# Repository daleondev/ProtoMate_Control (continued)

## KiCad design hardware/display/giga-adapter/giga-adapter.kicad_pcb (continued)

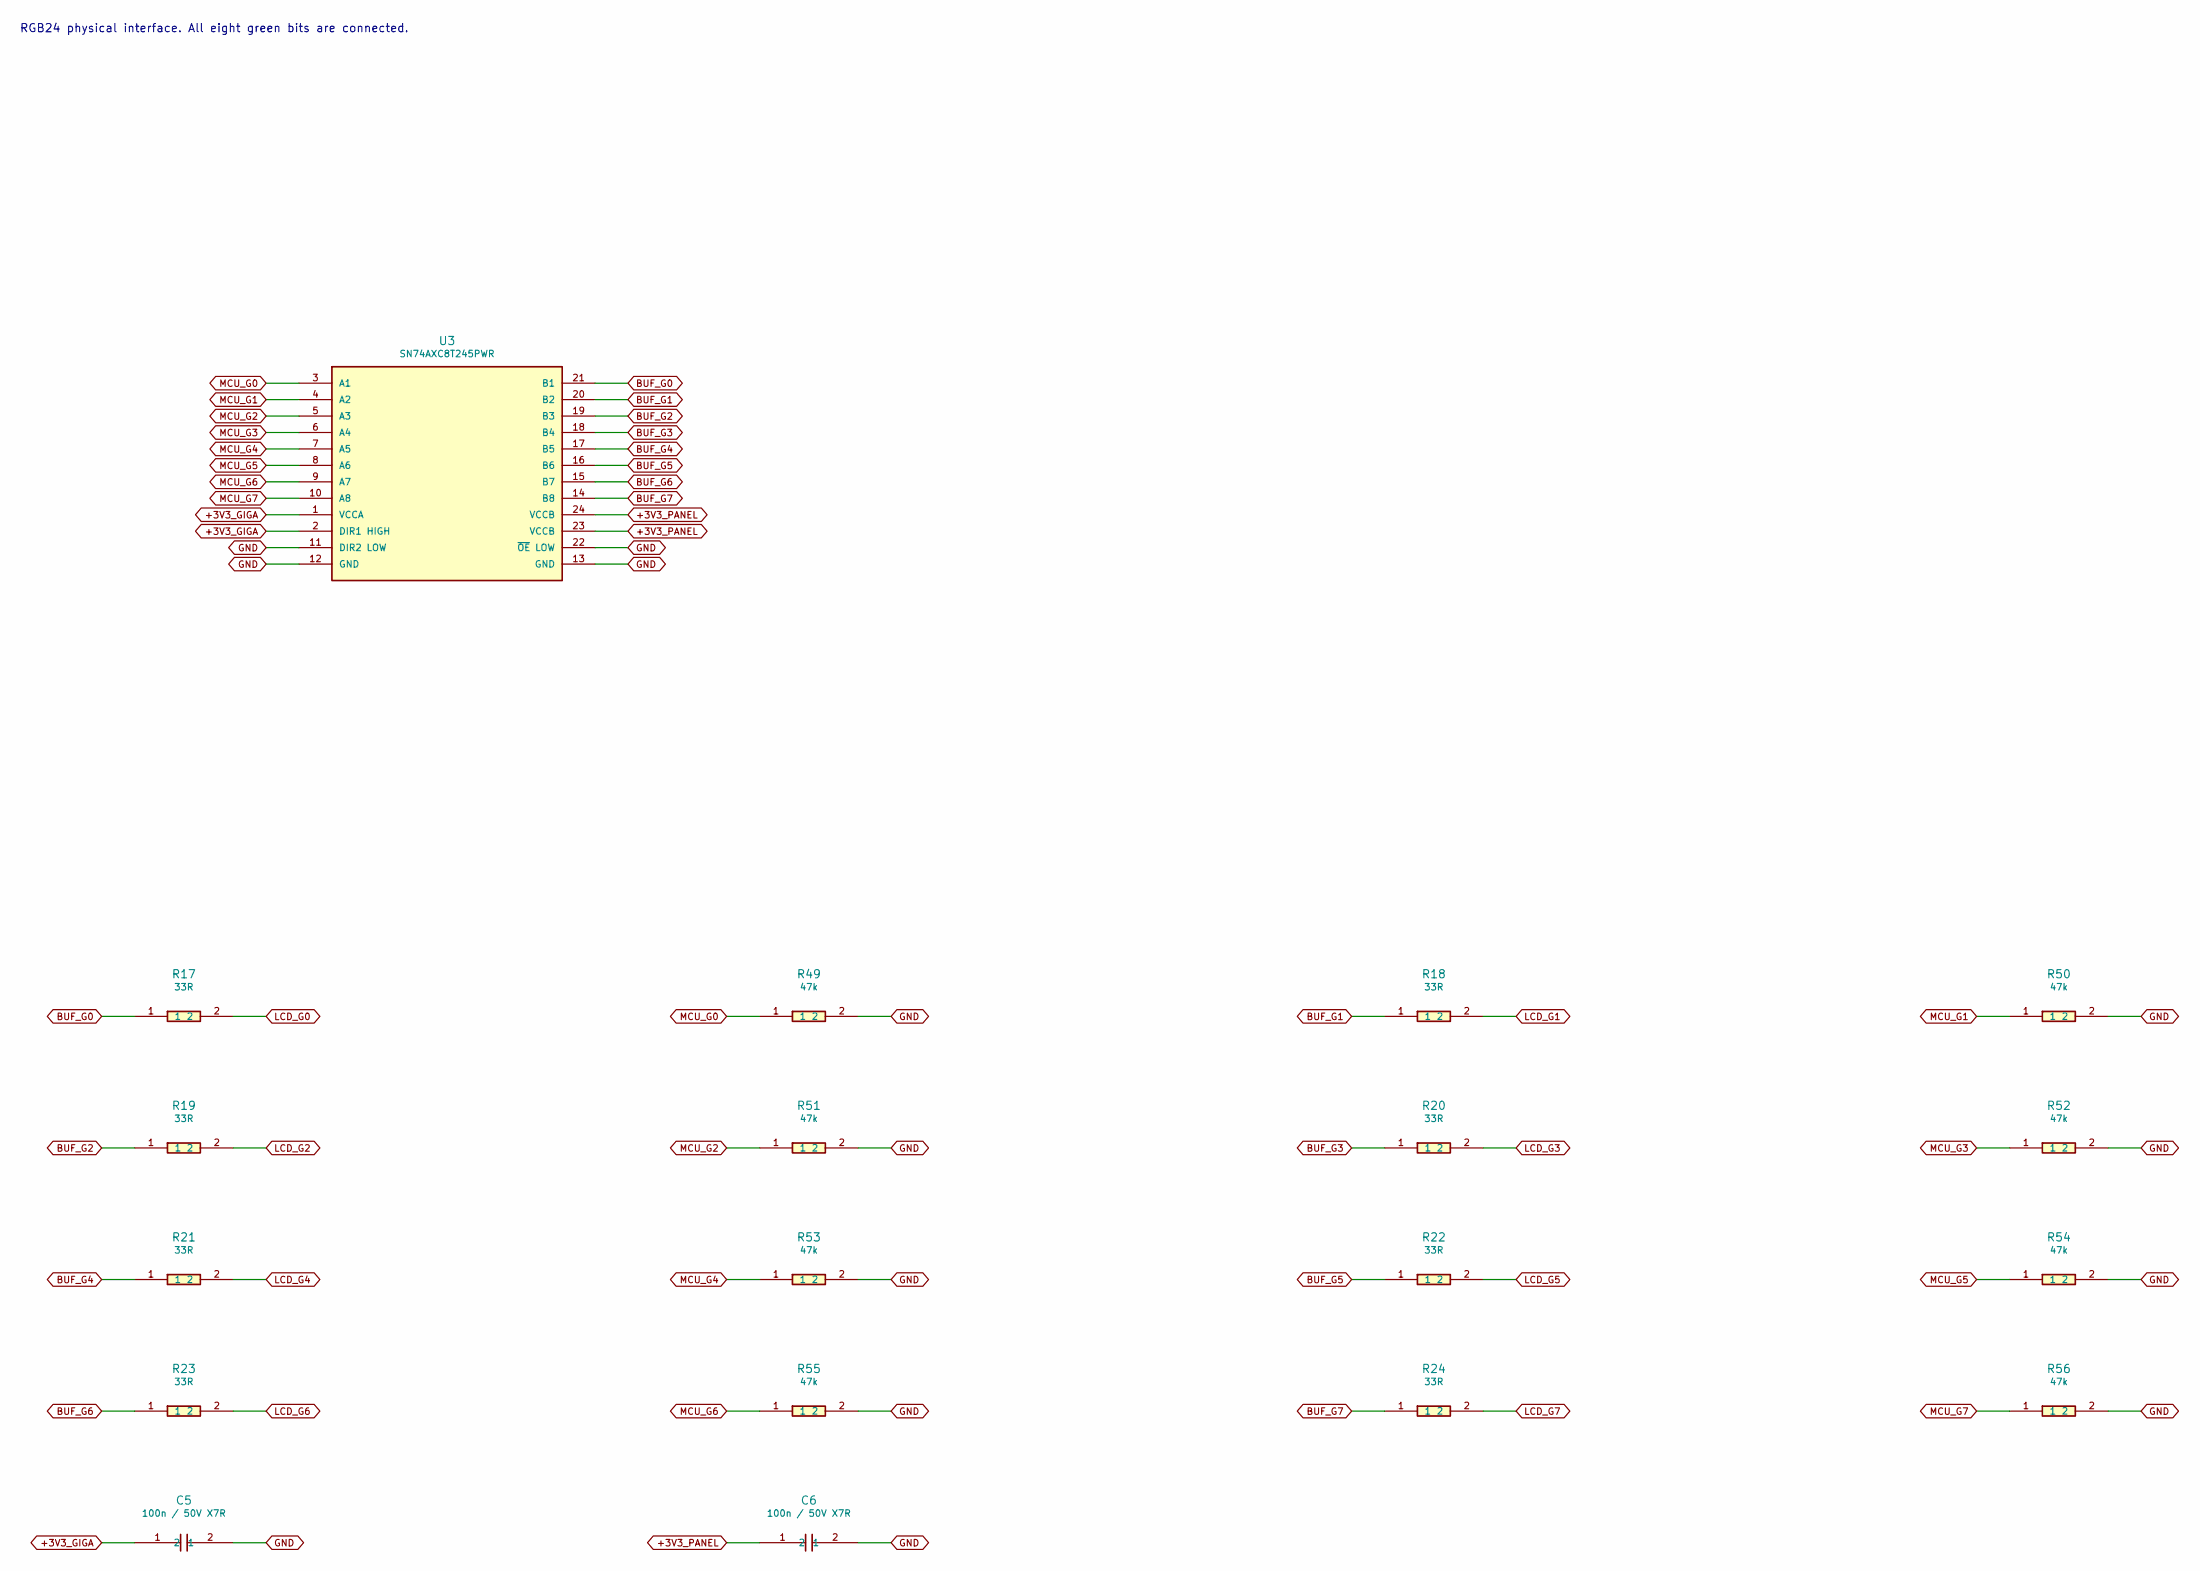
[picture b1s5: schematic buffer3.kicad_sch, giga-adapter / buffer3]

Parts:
C5, C6: 100n / 50V X7R; C_0603_1608Metric; MPN C0603C104K5RACTU
R17, R18, R19, R20, R21, R22, R23, R24: 33R; R_0402_1005Metric; MPN RC0402FR-0733RL
R49, R50, R51, R52, R53, R54, R55, R56: 47k; R_0402_1005Metric; MPN RC0402FR-0747KL
U3: SN74AXC8T245PWR; TSSOP-24_4.4x7.8mm_P0.65mm; MPN SN74AXC8T245PWR

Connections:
+3V3_GIGA: C5.1, U3.1 (VCCA), U3.2 (DIR1 HIGH); also elsewhere on the board
+3V3_PANEL: C6.1, U3.23 (VCCB), U3.24 (VCCB); also elsewhere on the board
BUF_G0: R17.1, U3.21 (B1)
BUF_G1: R18.1, U3.20 (B2)
BUF_G2: R19.1, U3.19 (B3)
BUF_G3: R20.1, U3.18 (B4)
BUF_G4: R21.1, U3.17 (B5)
BUF_G5: R22.1, U3.16 (B6)
BUF_G6: R23.1, U3.15 (B7)
BUF_G7: R24.1, U3.14 (B8)
GND: C5.2, C6.2, R49.2, R50.2, R51.2, R52.2, R53.2, R54.2, R55.2, R56.2, U3.11 (DIR2 LOW), U3.12 (GND), U3.13 (GND), U3.22 (~OE LOW); also elsewhere on the board
LCD_G0: R17.2; also elsewhere on the board
LCD_G1: R18.2; also elsewhere on the board
LCD_G2: R19.2; also elsewhere on the board
LCD_G3: R20.2; also elsewhere on the board
LCD_G4: R21.2; also elsewhere on the board
LCD_G5: R22.2; also elsewhere on the board
LCD_G6: R23.2; also elsewhere on the board
LCD_G7: R24.2; also elsewhere on the board
MCU_G0: R49.1, U3.3 (A1); also elsewhere on the board
MCU_G1: R50.1, U3.4 (A2); also elsewhere on the board
MCU_G2: R51.1, U3.5 (A3); also elsewhere on the board
MCU_G3: R52.1, U3.6 (A4); also elsewhere on the board
MCU_G4: R53.1, U3.7 (A5); also elsewhere on the board
MCU_G5: R54.1, U3.8 (A6); also elsewhere on the board
MCU_G6: R55.1, U3.9 (A7); also elsewhere on the board
MCU_G7: R56.1, U3.10 (A8); also elsewhere on the board

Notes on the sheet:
RGB24 physical interface. All eight green bits are connected.

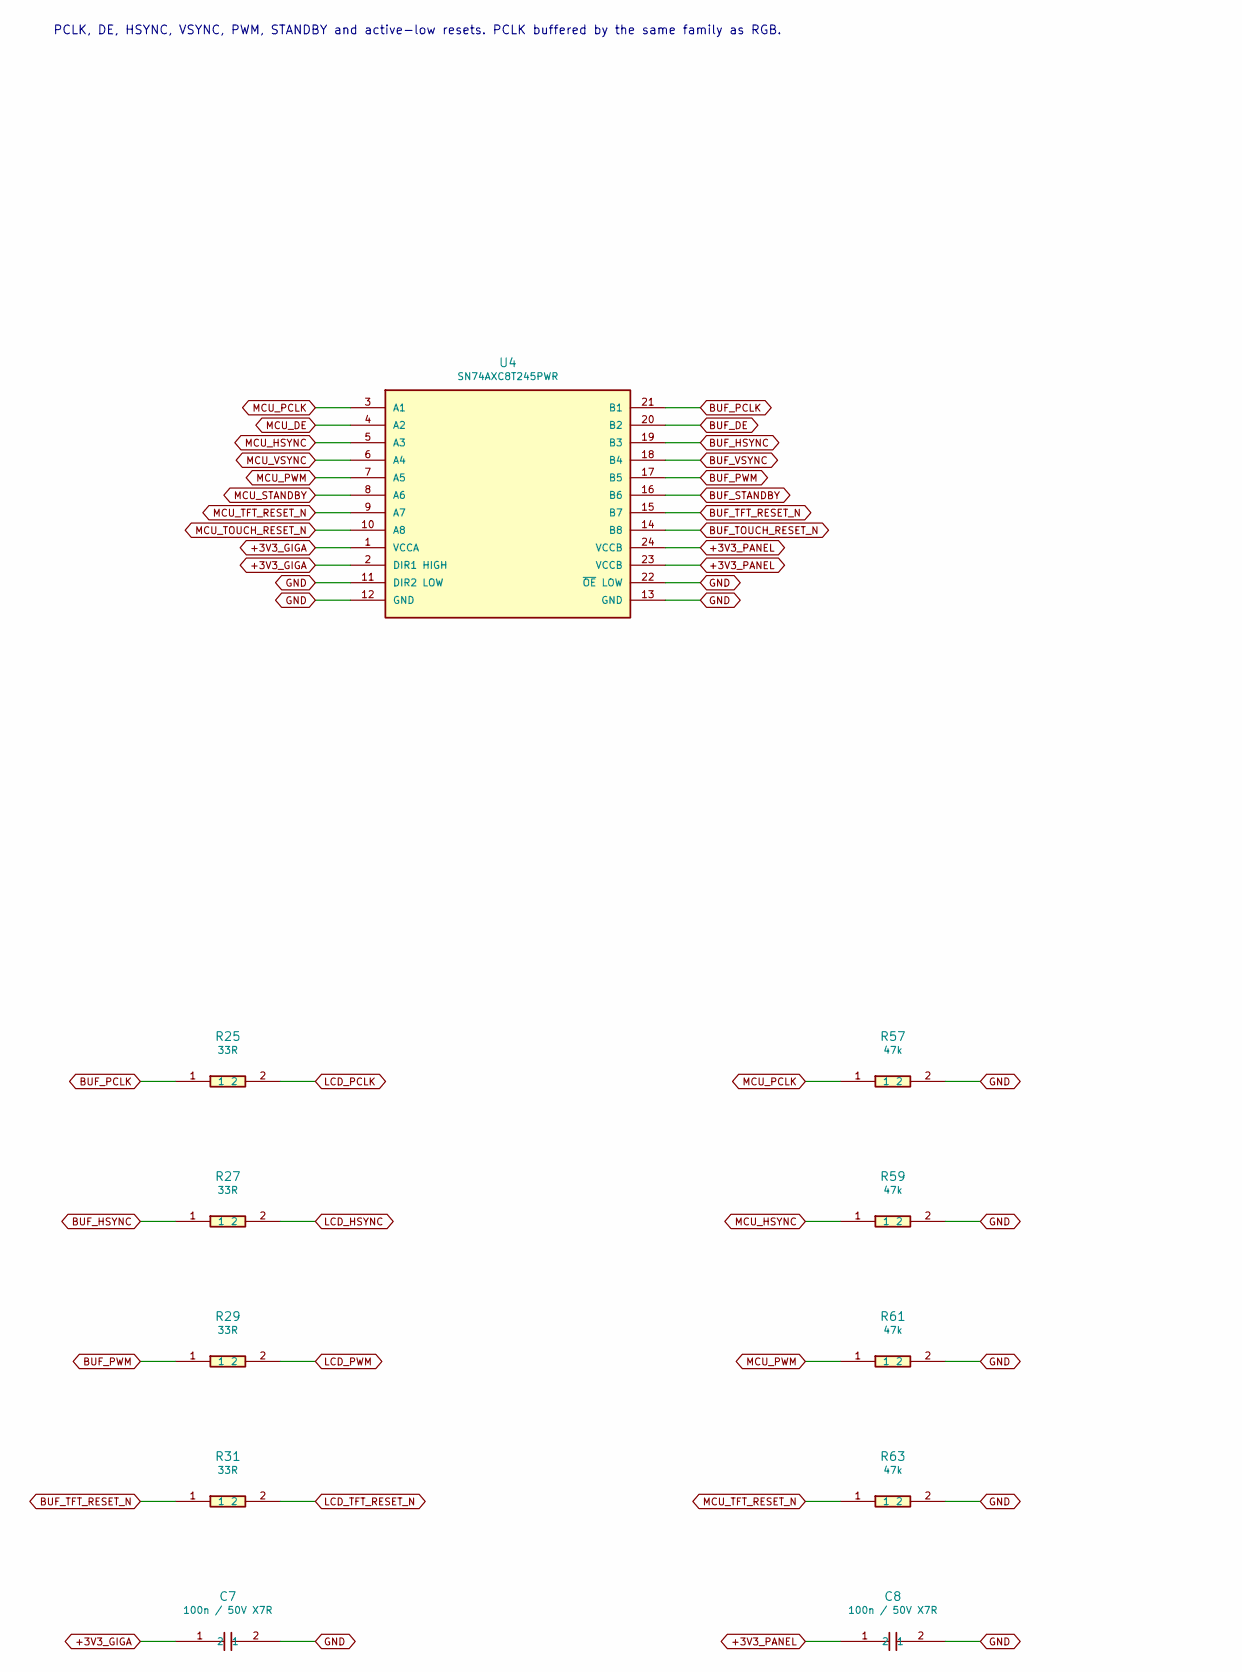
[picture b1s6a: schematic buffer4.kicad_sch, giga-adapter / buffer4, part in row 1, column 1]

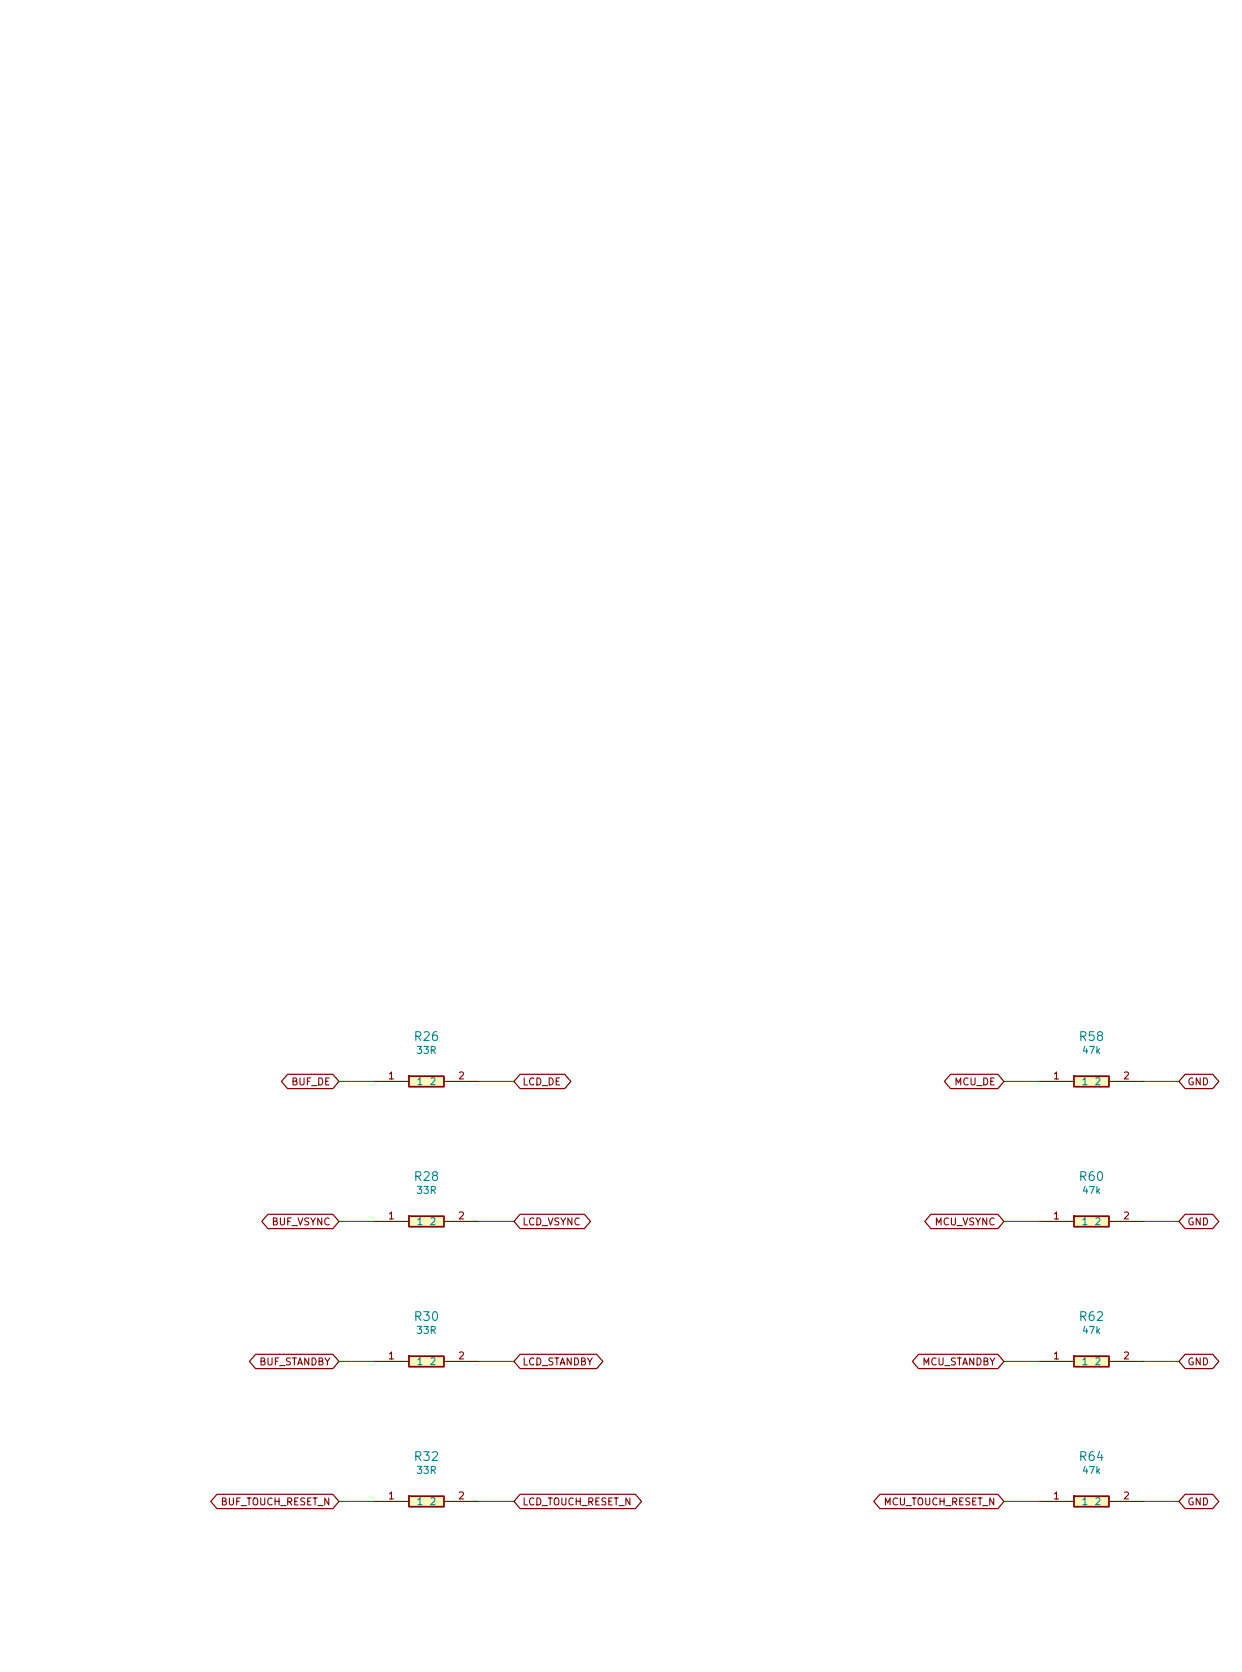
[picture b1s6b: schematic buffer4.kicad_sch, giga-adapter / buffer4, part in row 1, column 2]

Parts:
C7, C8: 100n / 50V X7R; C_0603_1608Metric; MPN C0603C104K5RACTU
R25, R26, R27, R28, R29, R30, R31, R32: 33R; R_0402_1005Metric; MPN RC0402FR-0733RL
R57, R58, R59, R60, R61, R62, R63, R64: 47k; R_0402_1005Metric; MPN RC0402FR-0747KL
U4: SN74AXC8T245PWR; TSSOP-24_4.4x7.8mm_P0.65mm; MPN SN74AXC8T245PWR

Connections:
+3V3_GIGA: C7.1, U4.1 (VCCA), U4.2 (DIR1 HIGH); also elsewhere on the board
+3V3_PANEL: C8.1, U4.23 (VCCB), U4.24 (VCCB); also elsewhere on the board
BUF_DE: R26.1, U4.20 (B2)
BUF_HSYNC: R27.1, U4.19 (B3)
BUF_PCLK: R25.1, U4.21 (B1)
BUF_PWM: R29.1, U4.17 (B5)
BUF_STANDBY: R30.1, U4.16 (B6)
BUF_TFT_RESET_N: R31.1, U4.15 (B7)
BUF_TOUCH_RESET_N: R32.1, U4.14 (B8)
BUF_VSYNC: R28.1, U4.18 (B4)
GND: C7.2, C8.2, R57.2, R58.2, R59.2, R60.2, R61.2, R62.2, R63.2, R64.2, U4.11 (DIR2 LOW), U4.12 (GND), U4.13 (GND), U4.22 (~OE LOW); also elsewhere on the board
LCD_DE: R26.2; also elsewhere on the board
LCD_HSYNC: R27.2; also elsewhere on the board
LCD_PCLK: R25.2; also elsewhere on the board
LCD_PWM: R29.2; also elsewhere on the board
LCD_STANDBY: R30.2; also elsewhere on the board
LCD_TFT_RESET_N: R31.2; also elsewhere on the board
LCD_TOUCH_RESET_N: R32.2; also elsewhere on the board
LCD_VSYNC: R28.2; also elsewhere on the board
MCU_DE: R58.1, U4.4 (A2); also elsewhere on the board
MCU_HSYNC: R59.1, U4.5 (A3); also elsewhere on the board
MCU_PCLK: R57.1, U4.3 (A1); also elsewhere on the board
MCU_PWM: R61.1, U4.7 (A5); also elsewhere on the board
MCU_STANDBY: R62.1, U4.8 (A6); also elsewhere on the board
MCU_TFT_RESET_N: R63.1, U4.9 (A7); also elsewhere on the board
MCU_TOUCH_RESET_N: R64.1, U4.10 (A8); also elsewhere on the board
MCU_VSYNC: R60.1, U4.6 (A4); also elsewhere on the board

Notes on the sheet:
PCLK, DE, HSYNC, VSYNC, PWM, STANDBY and active-low resets. PCLK buffered by the same family as RGB.

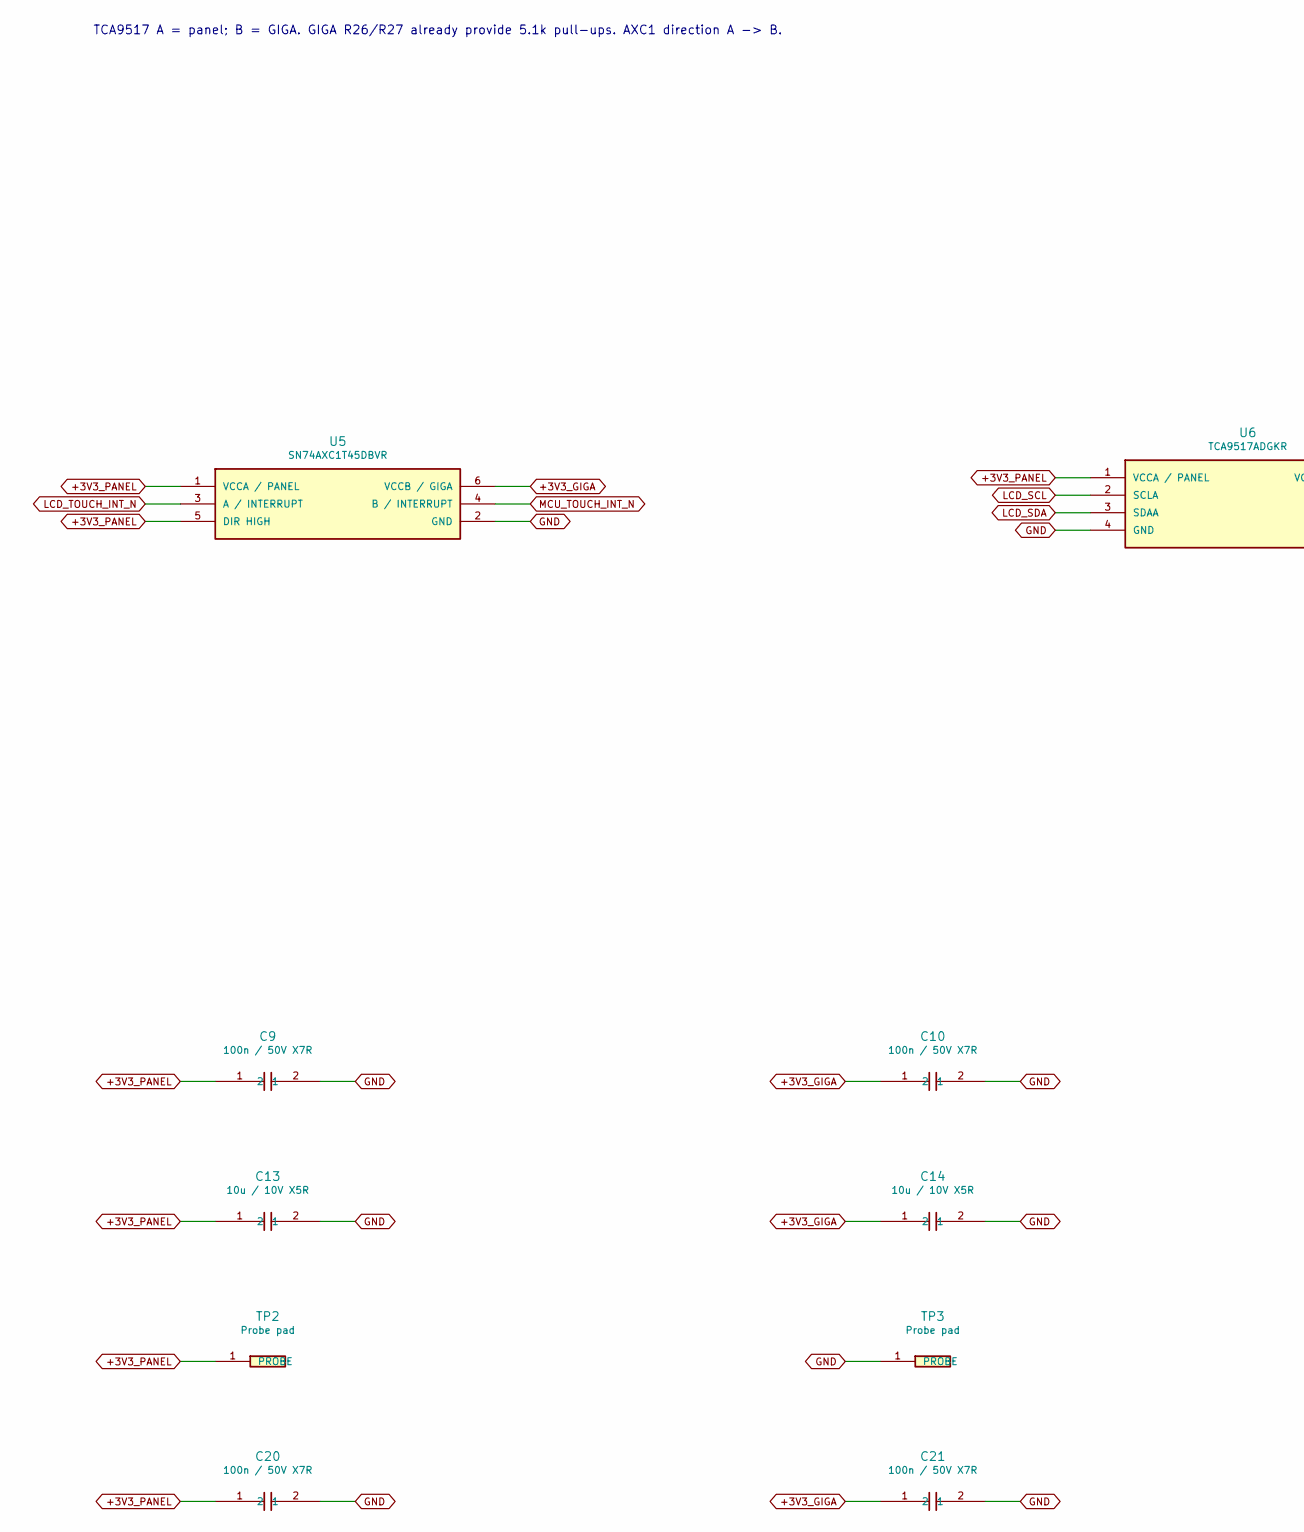
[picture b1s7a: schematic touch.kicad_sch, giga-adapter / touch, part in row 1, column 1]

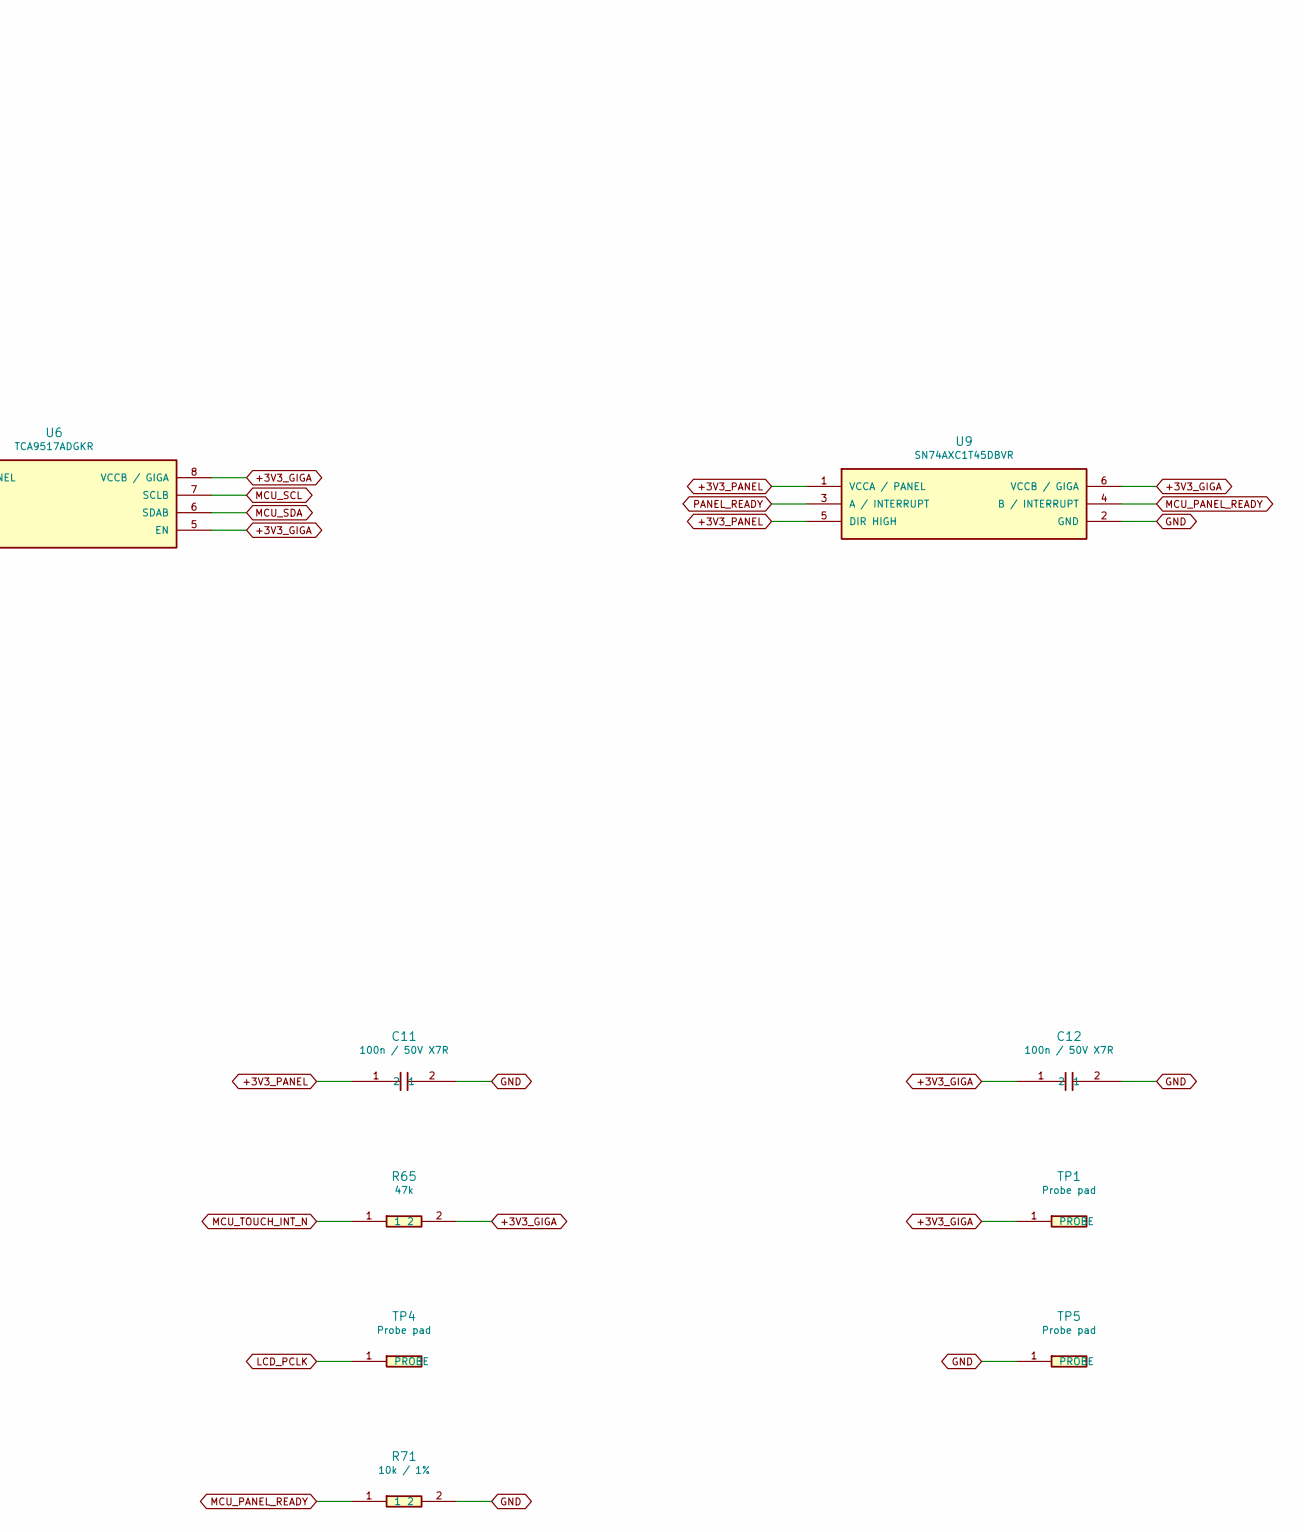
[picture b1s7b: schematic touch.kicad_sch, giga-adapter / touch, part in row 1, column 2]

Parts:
C9, C10, C11, C12, C20, C21: 100n / 50V X7R; C_0603_1608Metric; MPN C0603C104K5RACTU
C13, C14: 10u / 10V X5R; C_0805_2012Metric; MPN C0805C106K8PACTU
R65: 47k; R_0402_1005Metric; MPN RC0402FR-0747KL
R71: 10k / 1%; R_0603_1608Metric; MPN RC0603FR-0710KL
TP1, TP2, TP3, TP4, TP5: Probe pad; TestPoint_1.0mm; MPN PCB copper feature
U5, U9: SN74AXC1T45DBVR; SOT-23-6; MPN SN74AXC1T45DBVR
U6: TCA9517ADGKR; VSSOP-8_3x3mm_P0.65mm; MPN TCA9517ADGKR

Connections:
+3V3_GIGA: C10.1, C12.1, C14.1, C21.1, R65.2, TP1.1, U5.6 (VCCB / GIGA), U6.5 (EN), U6.8 (VCCB / GIGA), U9.6 (VCCB / GIGA); also elsewhere on the board
+3V3_PANEL: C9.1, C11.1, C13.1, C20.1, TP2.1, U5.1 (VCCA / PANEL), U5.5 (DIR HIGH), U6.1 (VCCA / PANEL), U9.1 (VCCA / PANEL), U9.5 (DIR HIGH); also elsewhere on the board
GND: C9.2, C10.2, C11.2, C12.2, C13.2, C14.2, C20.2, C21.2, R71.2, TP3.1, TP5.1, U5.2 (GND), U6.4 (GND), U9.2 (GND); also elsewhere on the board
LCD_PCLK: TP4.1; also elsewhere on the board
LCD_SCL: U6.2 (SCLA); also elsewhere on the board
LCD_SDA: U6.3 (SDAA); also elsewhere on the board
LCD_TOUCH_INT_N: U5.3 (A / INTERRUPT); also elsewhere on the board
MCU_PANEL_READY: R71.1, U9.4 (B / INTERRUPT); also elsewhere on the board
MCU_SCL: U6.7 (SCLB); also elsewhere on the board
MCU_SDA: U6.6 (SDAB); also elsewhere on the board
MCU_TOUCH_INT_N: R65.1, U5.4 (B / INTERRUPT); also elsewhere on the board
PANEL_READY: U9.3 (A / INTERRUPT); also elsewhere on the board

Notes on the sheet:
TCA9517 A = panel; B = GIGA. GIGA R26/R27 already provide 5.1k pull-ups. AXC1 direction A -> B.

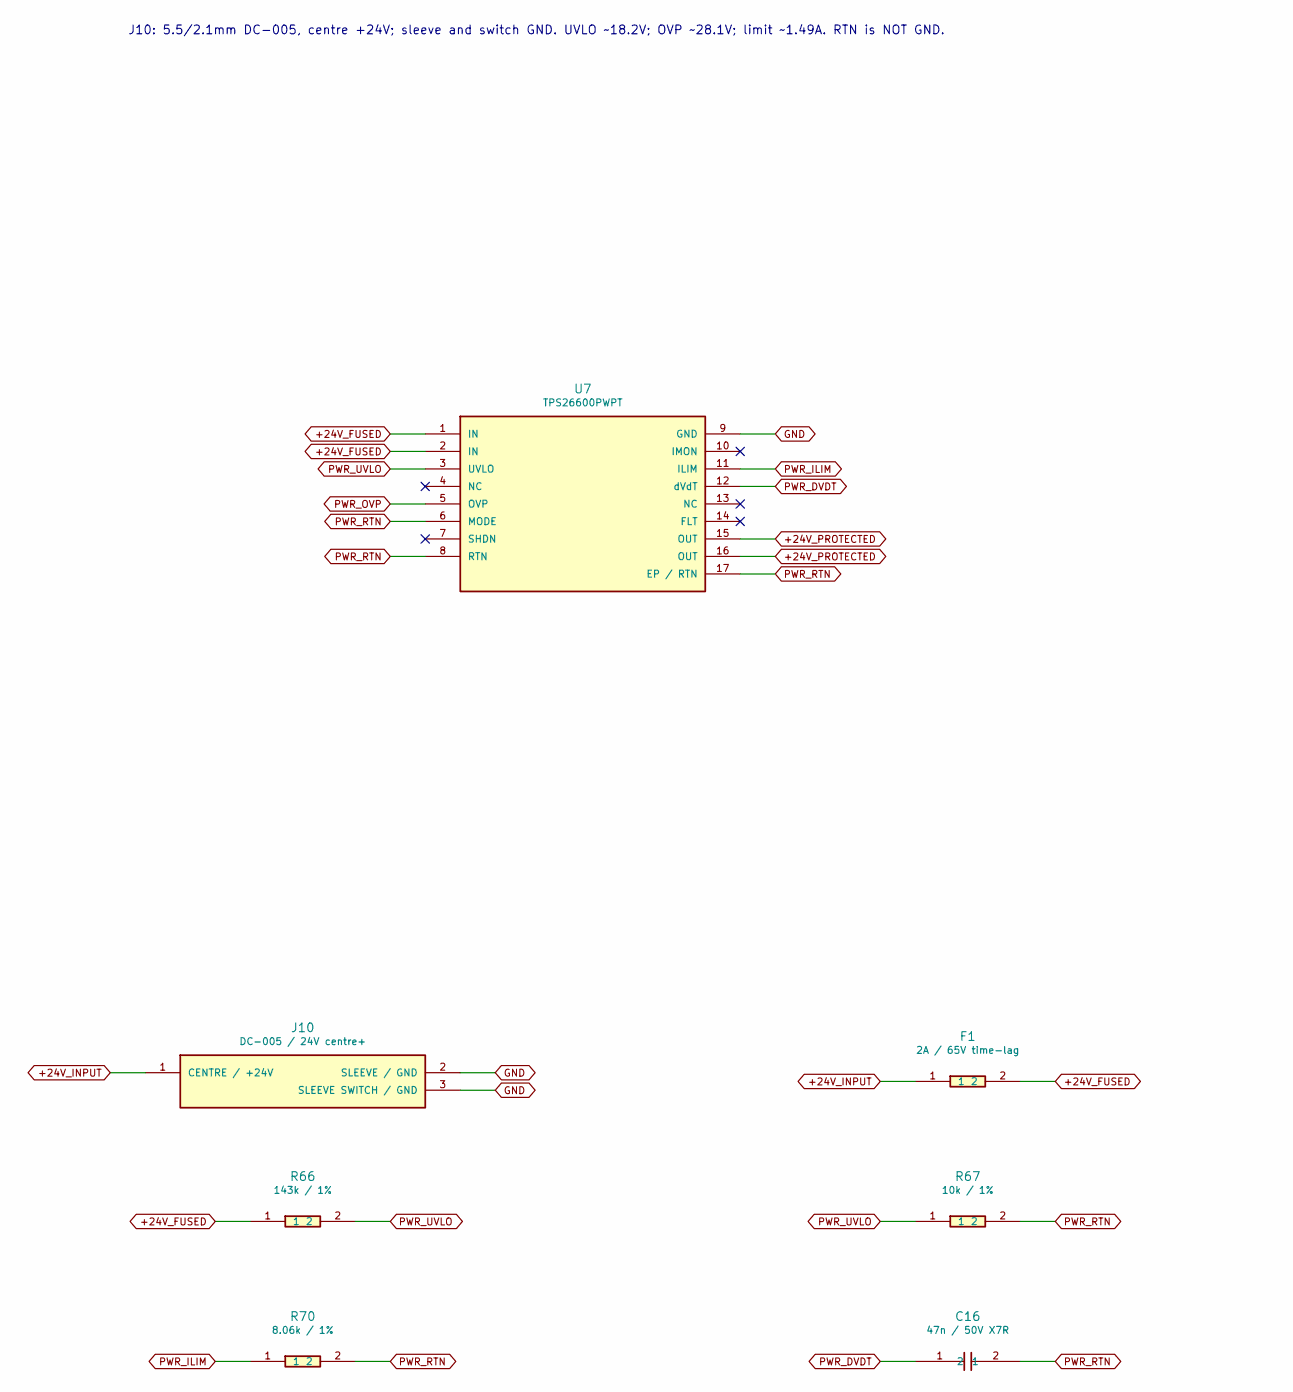
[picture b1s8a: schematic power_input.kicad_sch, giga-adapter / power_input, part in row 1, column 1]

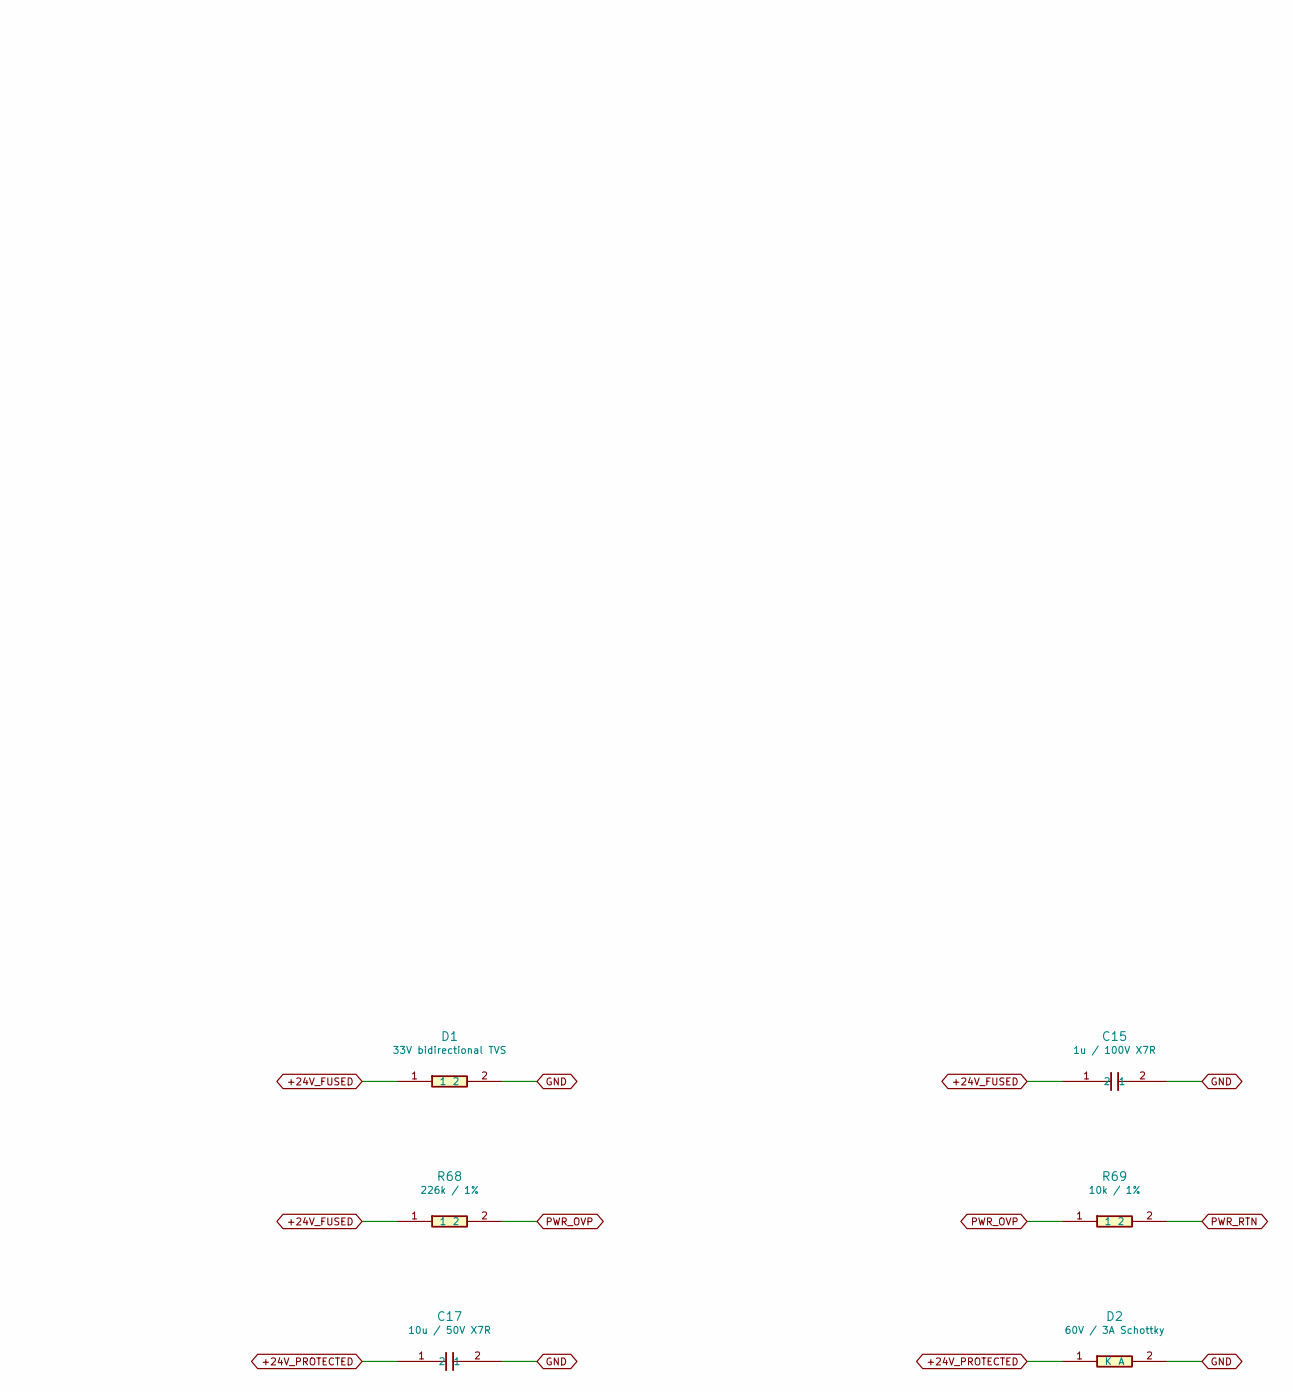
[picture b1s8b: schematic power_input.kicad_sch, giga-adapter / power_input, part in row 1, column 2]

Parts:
C15: 1u / 100V X7R; C_1206_3216Metric; MPN C1206C105K1RACTU
C16: 47n / 50V X7R; C_0603_1608Metric; MPN C1608X7R1H473K080AA
C17: 10u / 50V X7R; C_1210_3225Metric; MPN MCJCU32MLB7106KPPDTJ
D1: 33V bidirectional TVS; D_SMB; MPN SMBJ33CA-13-F
D2: 60V / 3A Schottky; D_SMA; MPN B360A-13-F
F1: 2A / 65V time-lag; Fuse_Bourns_SF-1206SA-M; MPN SF-1206SA200M-2
J10: DC-005 / 24V centre+; BarrelJack_Horizontal_AISLER; MPN DC-005 / B07J4Z8B2T
R66: 143k / 1%; R_0603_1608Metric; MPN RC0603FR-07143KL
R67, R69: 10k / 1%; R_0603_1608Metric; MPN RC0603FR-0710KL
R68: 226k / 1%; R_0603_1608Metric; MPN RC0603FR-07226KL
R70: 8.06k / 1%; R_0603_1608Metric; MPN RC0603FR-078K06L
U7: TPS26600PWPT; HTSSOP-16_PWP0016A_EP3.3x3.3mm; MPN TPS26600PWPT

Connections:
+24V_FUSED: C15.1, D1.1, F1.2, R66.1, R68.1, U7.1 (IN), U7.2 (IN)
+24V_INPUT: F1.1, J10.1 (CENTRE / +24V)
+24V_PROTECTED: C17.1, D2.1 (K), U7.15 (OUT), U7.16 (OUT); also elsewhere on the board
GND: C15.2, C17.2, D1.2, D2.2 (A), J10.2 (SLEEVE / GND), J10.3 (SLEEVE SWITCH / GND), U7.9 (GND); also elsewhere on the board
PWR_DVDT: C16.1, U7.12 (dVdT)
PWR_ILIM: R70.1, U7.11 (ILIM)
PWR_OVP: R68.2, R69.1, U7.5 (OVP)
PWR_RTN: C16.2, R67.2, R69.2, R70.2, U7.6 (MODE), U7.8 (RTN), U7.17 (EP / RTN)
PWR_UVLO: R66.2, R67.1, U7.3 (UVLO)

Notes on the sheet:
J10: 5.5/2.1mm DC-005, centre +24V; sleeve and switch GND. UVLO ~18.2V; OVP ~28.1V; limit ~1.49A. RTN is NOT GND.

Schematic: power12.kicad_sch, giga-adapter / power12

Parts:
C18: 10u / 50V X7R; C_1210_3225Metric; MPN MCJCU32MLB7106KPPDTJ
C19: 10u / 25V X5R; C_0805_2012Metric; MPN 08053D106KAT2A
D3: 60V / 3A Schottky; D_SMA; MPN B360A-13-F
F2: 0.8A / 63V time-lag; Fuse_1206_3216Metric; MPN SF-1206S080-2
TP6, TP7: Probe pad; TestPoint_1.0mm; MPN PCB copper feature
U8: TSR 1-24120 / 12V 1A; Converter_DCDC_TRACO_TSR-1_THT; MPN TSR 1-24120

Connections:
+12V_CONVERTER: C19.1, D3.2 (A), U8.3 (VOUT)
+12V_GIGA: D3.1 (K), TP7.1; also elsewhere on the board
+24V_DISPLAY: F2.2; also elsewhere on the board
+24V_PROTECTED: C18.1, F2.1, TP6.1, U8.1 (VIN); also elsewhere on the board
GND: C18.2, C19.2, U8.2 (GND); also elsewhere on the board

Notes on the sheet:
U8: 24V -> 12V / 1A. D3 blocks USB-only reverse feed into U8. F2 protects the two parallel 24V ribbon conductors.

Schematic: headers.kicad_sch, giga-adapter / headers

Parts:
J2: JDIGITAL 1..10; GIGA_J2_JDIGITAL; MPN SSQ-110-03-G-S
J3: JDIGITAL 11..18; GIGA_J3_JDIGITAL; MPN SSQ-108-03-G-S
J4: JDIGITAL 19..26; GIGA_J4_JDIGITAL; MPN SSQ-108-03-G-S
J5: JANALOG 1..8; GIGA_J5_JANALOG; MPN SSQ-108-03-G-S
J6: JANALOG 9..16; GIGA_J6_JANALOG; MPN SSQ-108-03-G-S
J7: JANALOG 17..24; GIGA_J7_JANALOG; MPN SSQ-108-03-G-S
J8: JSIDE 1..36; GIGA_J8_JSIDE; MPN SSQ-118-03-G-D
J9: J5 1..24; GIGA_J9_J5; MPN SSQ-112-04-G-D

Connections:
+3V3_GIGA: J5.2, J5.4, J9.23; also elsewhere on the board
+12V_GIGA: J5.8, J9.24; also elsewhere on the board
GND: J2.4, J5.6, J5.7, J8.35, J8.36, J9.3, J9.4, J9.7, J9.8, J9.11, J9.12, J9.22; also elsewhere on the board
MCU_B0: J8.3; also elsewhere on the board
MCU_B1: J8.5; also elsewhere on the board
MCU_B2: J8.7; also elsewhere on the board
MCU_B3: J8.9; also elsewhere on the board
MCU_B4: J8.11; also elsewhere on the board
MCU_B5: J8.13; also elsewhere on the board
MCU_B6: J8.15; also elsewhere on the board
MCU_B7: J8.17; also elsewhere on the board
MCU_DE: J8.22; also elsewhere on the board
MCU_G0: J8.19; also elsewhere on the board
MCU_G1: J8.21; also elsewhere on the board
MCU_G2: J8.23; also elsewhere on the board
MCU_G3: J8.25; also elsewhere on the board
MCU_G4: J8.27; also elsewhere on the board
MCU_G5: J8.29; also elsewhere on the board
MCU_G6: J8.31; also elsewhere on the board
MCU_G7: J8.33; also elsewhere on the board
MCU_HSYNC: J8.24; also elsewhere on the board
MCU_PANEL_READY: J9.15; also elsewhere on the board
MCU_PCLK: J8.20; also elsewhere on the board
MCU_PWM: J9.13; also elsewhere on the board
MCU_R0: J8.4; also elsewhere on the board
MCU_R1: J8.6; also elsewhere on the board
MCU_R2: J8.8; also elsewhere on the board
MCU_R3: J8.10; also elsewhere on the board
MCU_R4: J8.12; also elsewhere on the board
MCU_R5: J8.14; also elsewhere on the board
MCU_R6: J8.16; also elsewhere on the board
MCU_R7: J8.18; also elsewhere on the board
MCU_SCL: J2.1; also elsewhere on the board
MCU_SDA: J2.2; also elsewhere on the board
MCU_STANDBY: J9.14; also elsewhere on the board
MCU_TFT_RESET_N: J9.16; also elsewhere on the board
MCU_TOUCH_INT_N: J9.19; also elsewhere on the board
MCU_TOUCH_RESET_N: J9.17; also elsewhere on the board
MCU_VSYNC: J8.26; also elsewhere on the board

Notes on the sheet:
NC means no adapter trace. Socket still passes that GIGA contact straight through. Do not populate other header variants.
